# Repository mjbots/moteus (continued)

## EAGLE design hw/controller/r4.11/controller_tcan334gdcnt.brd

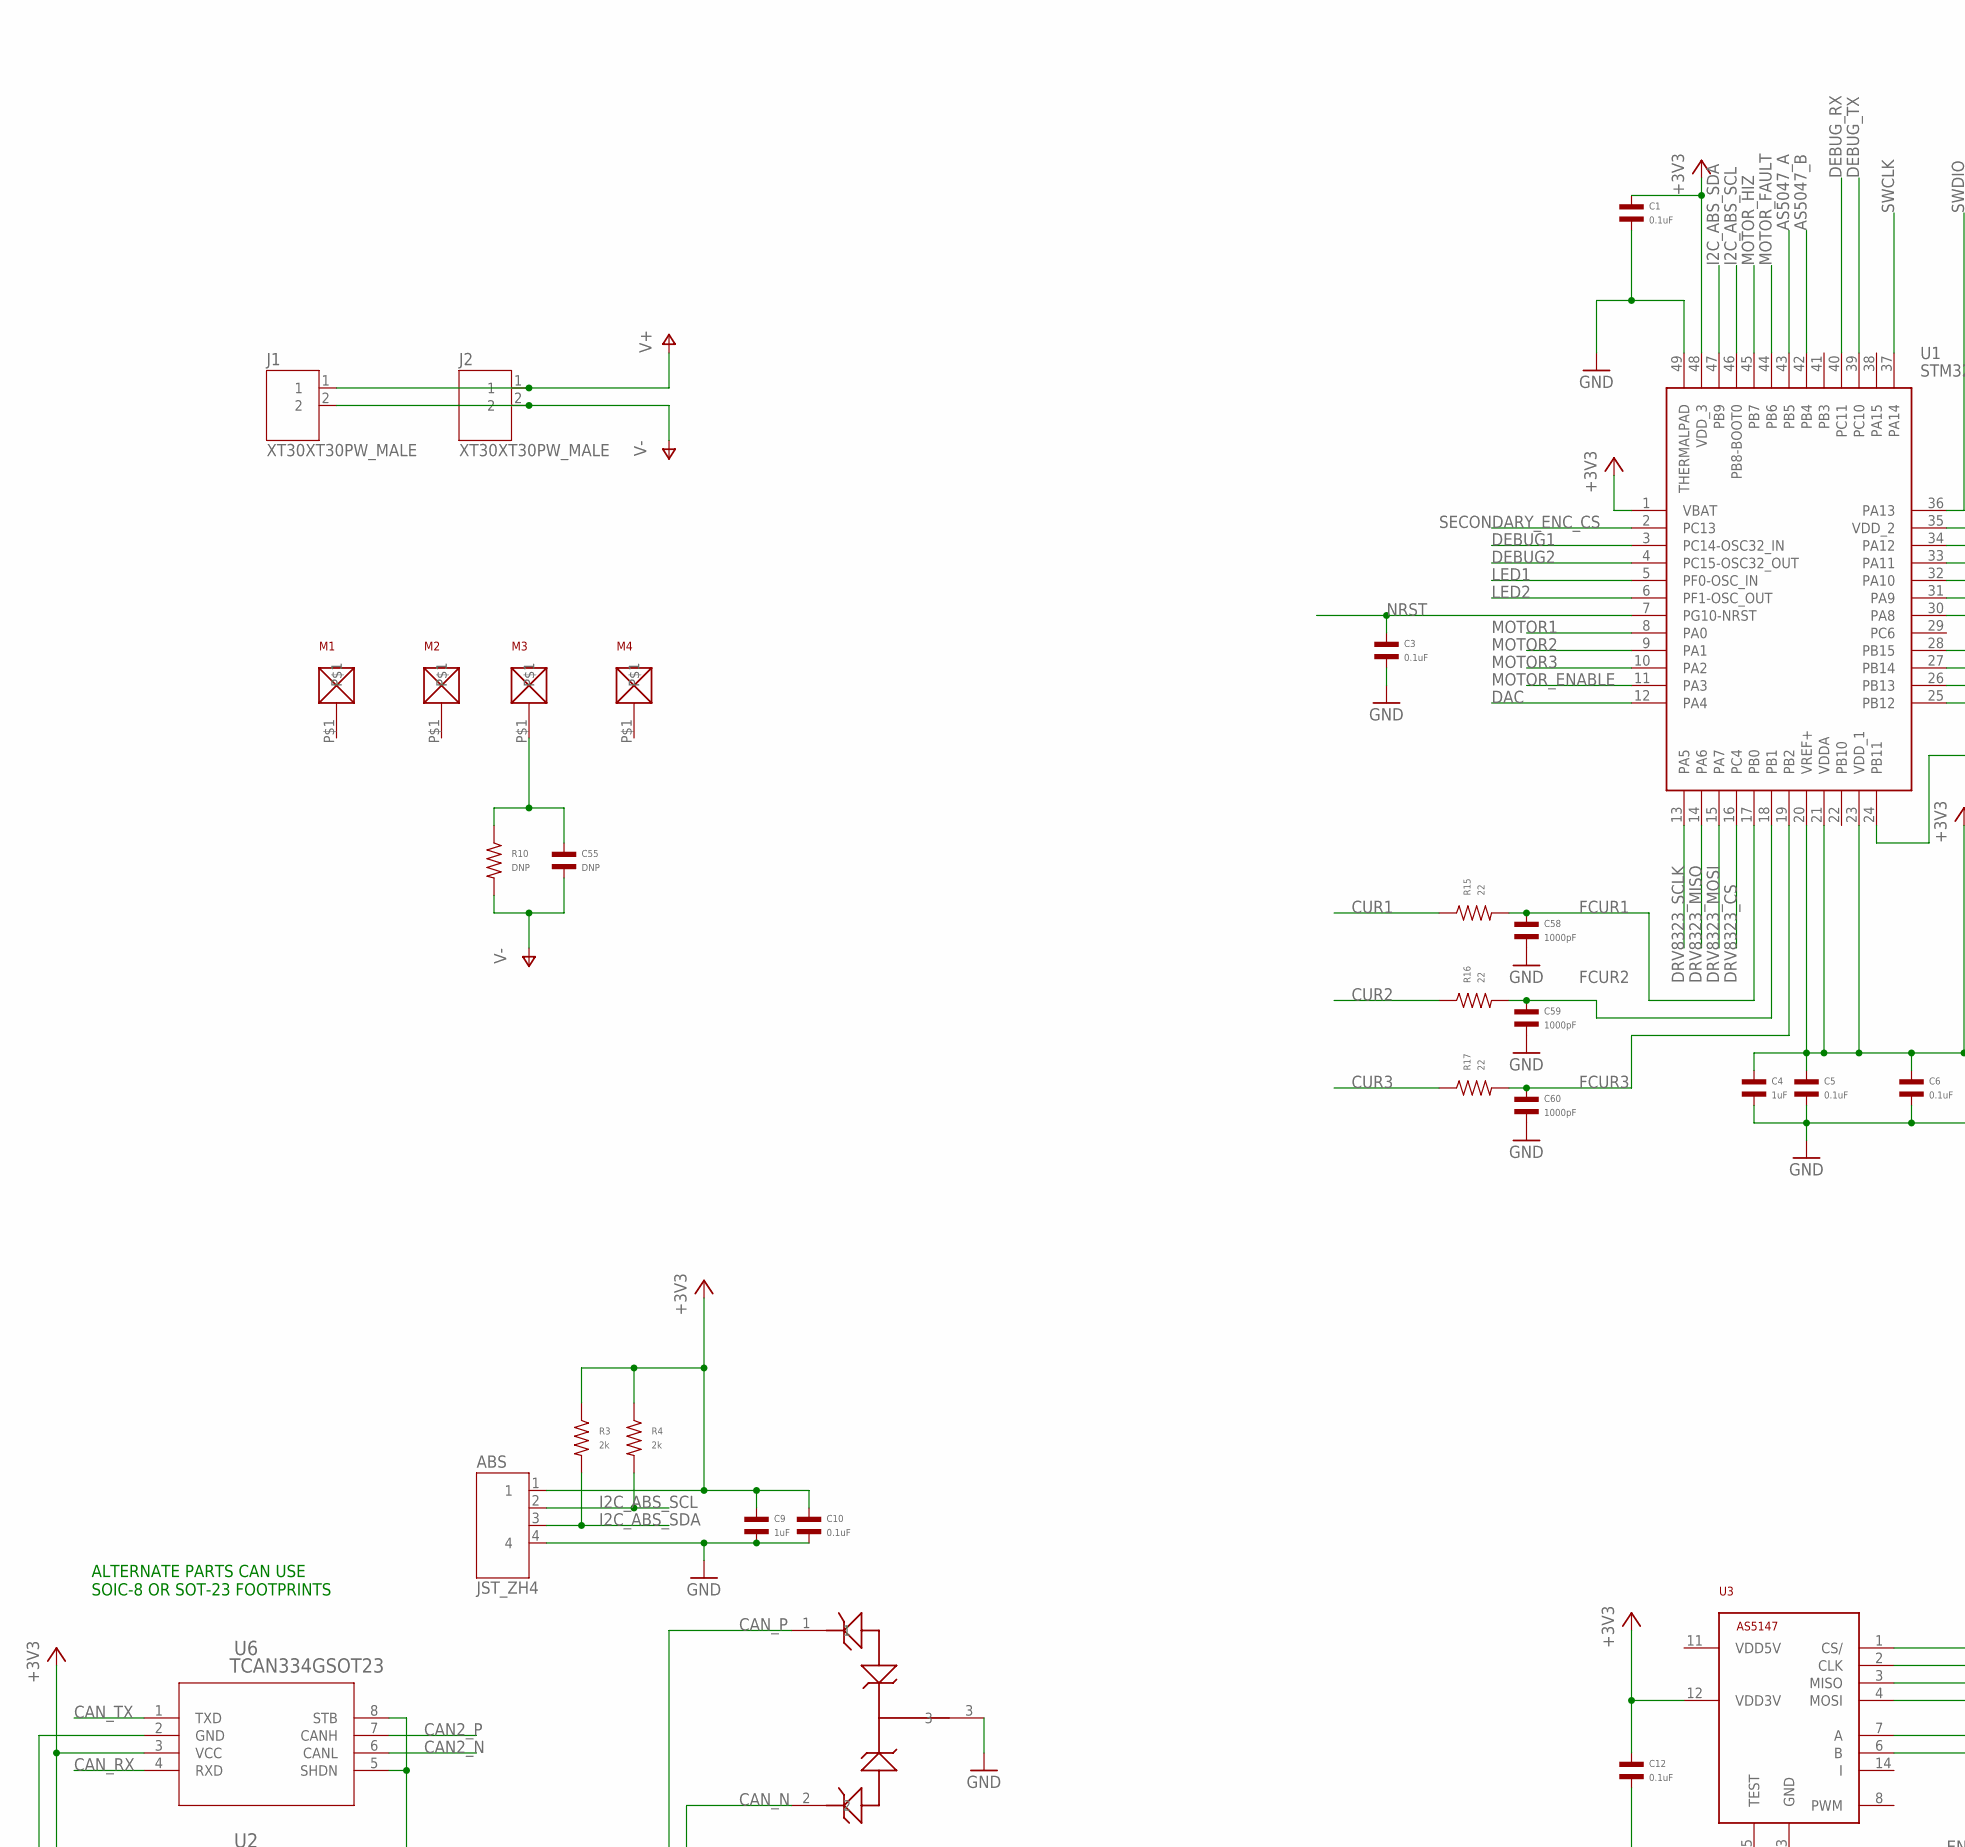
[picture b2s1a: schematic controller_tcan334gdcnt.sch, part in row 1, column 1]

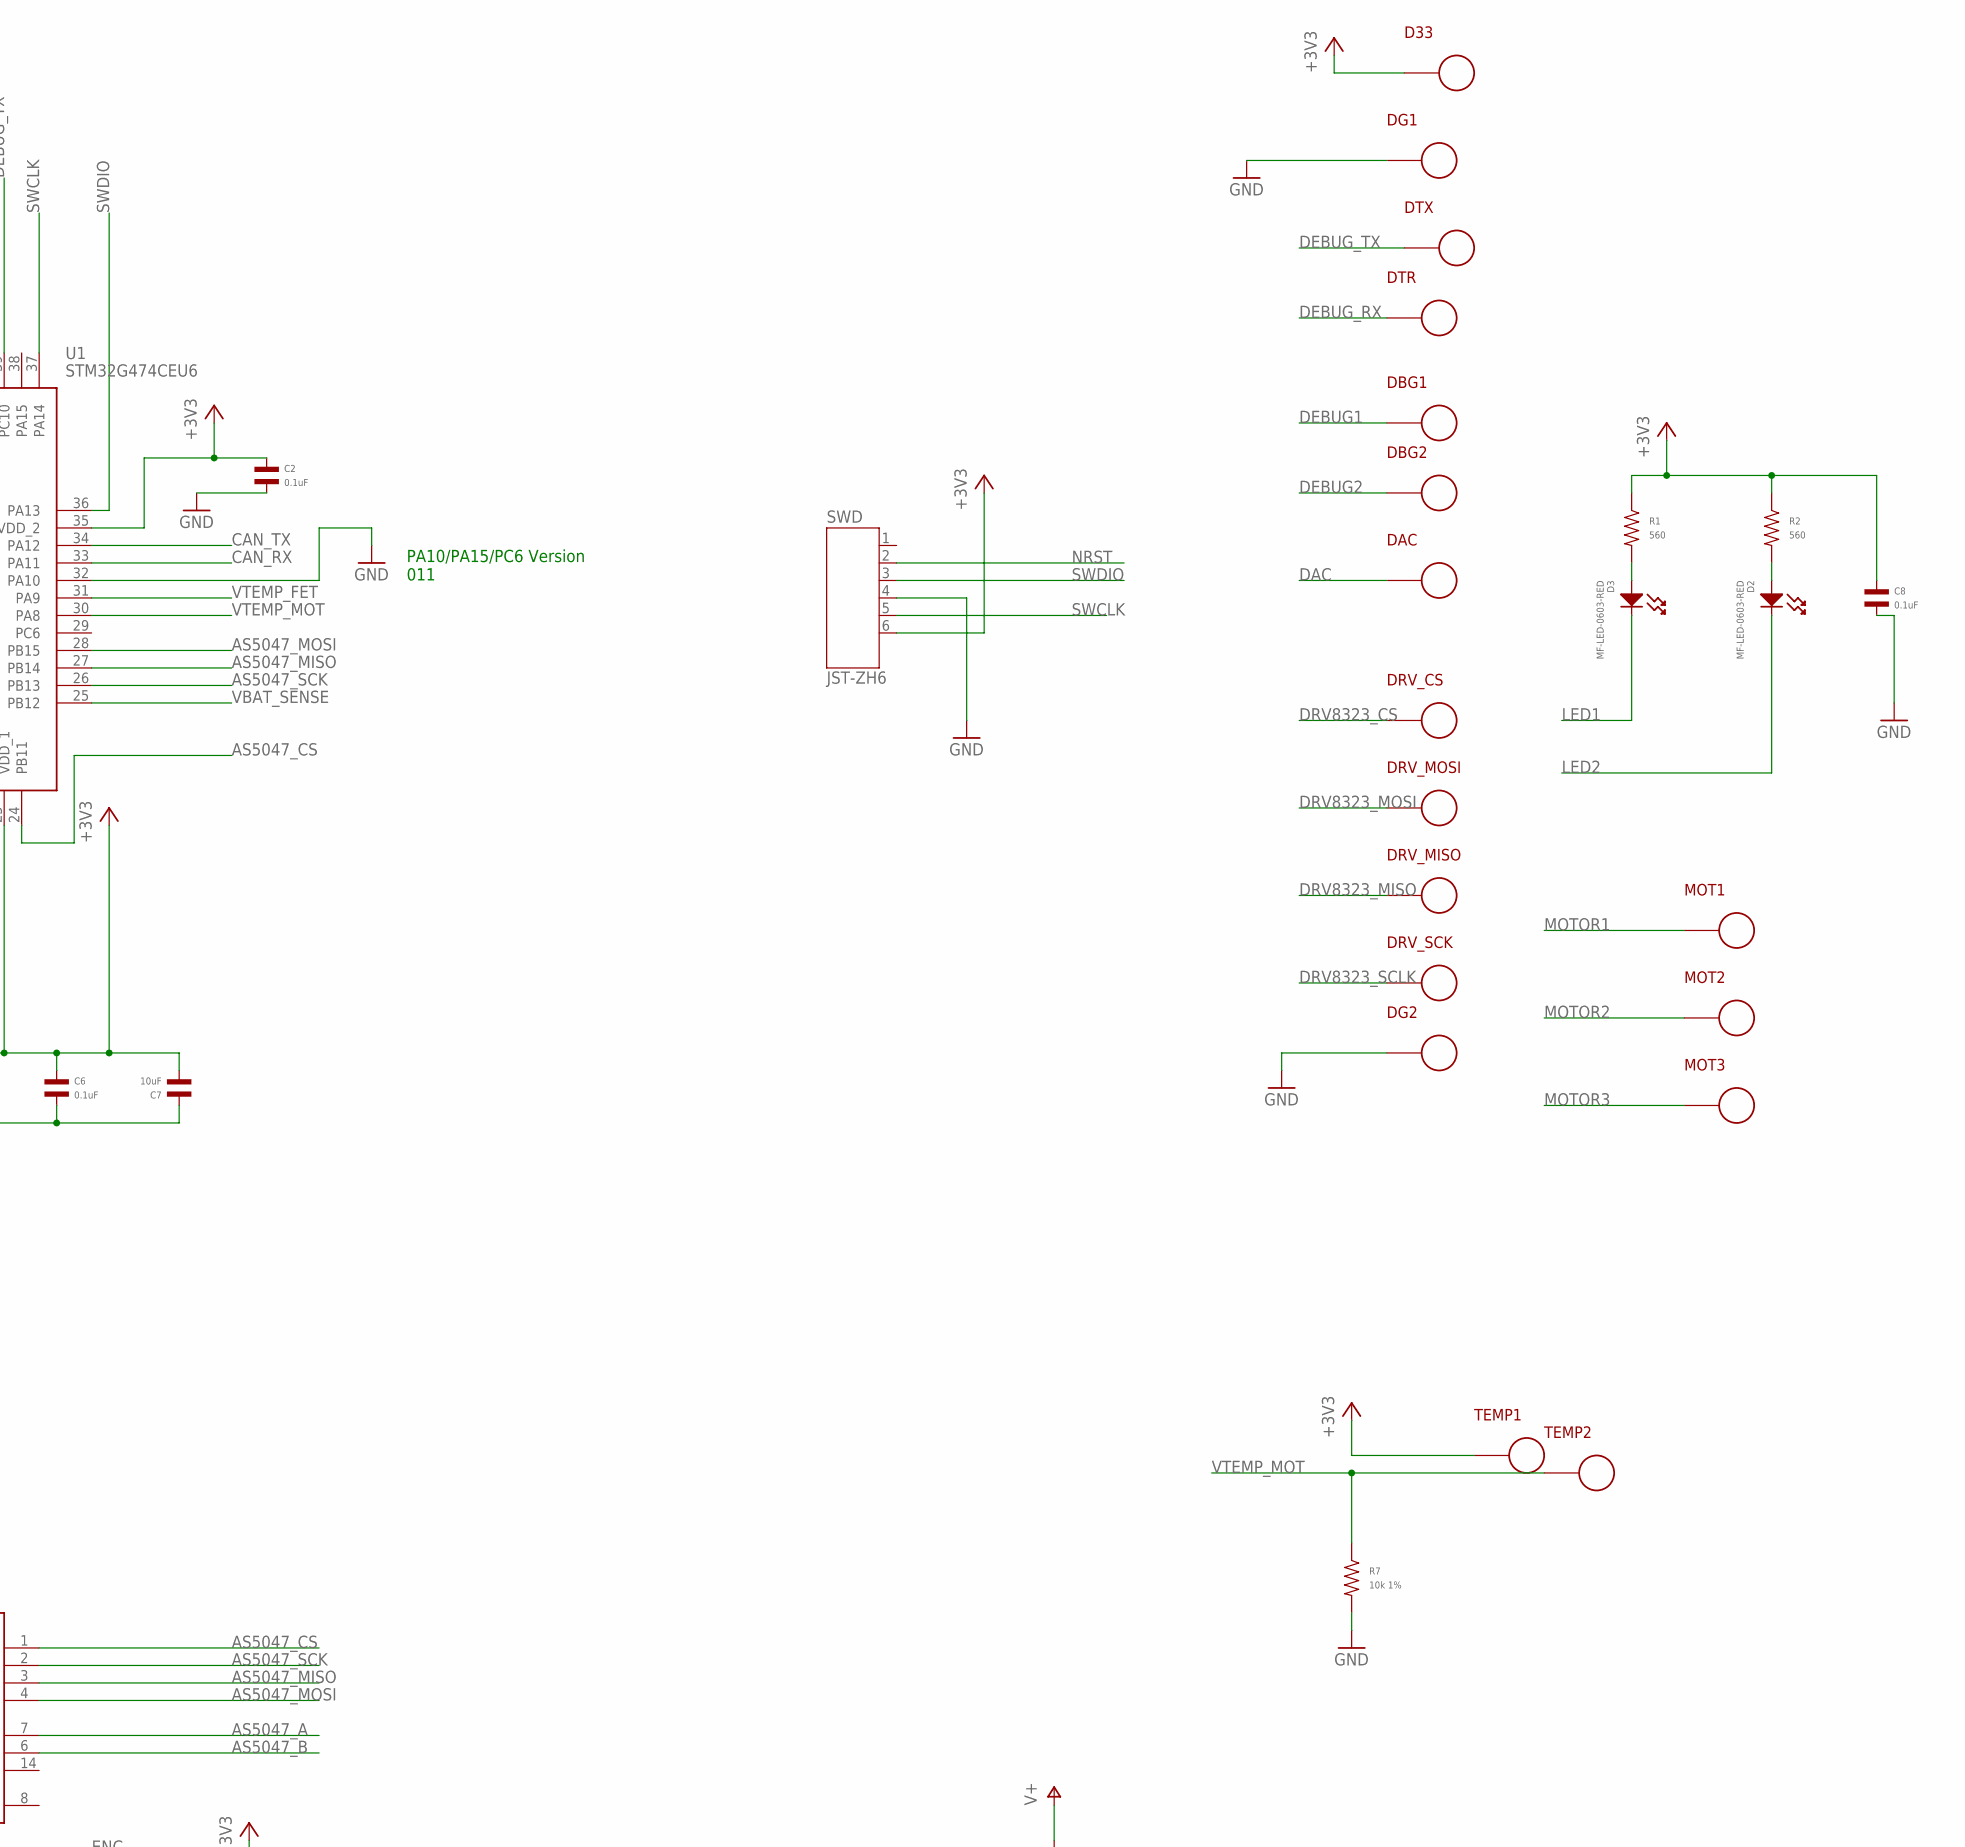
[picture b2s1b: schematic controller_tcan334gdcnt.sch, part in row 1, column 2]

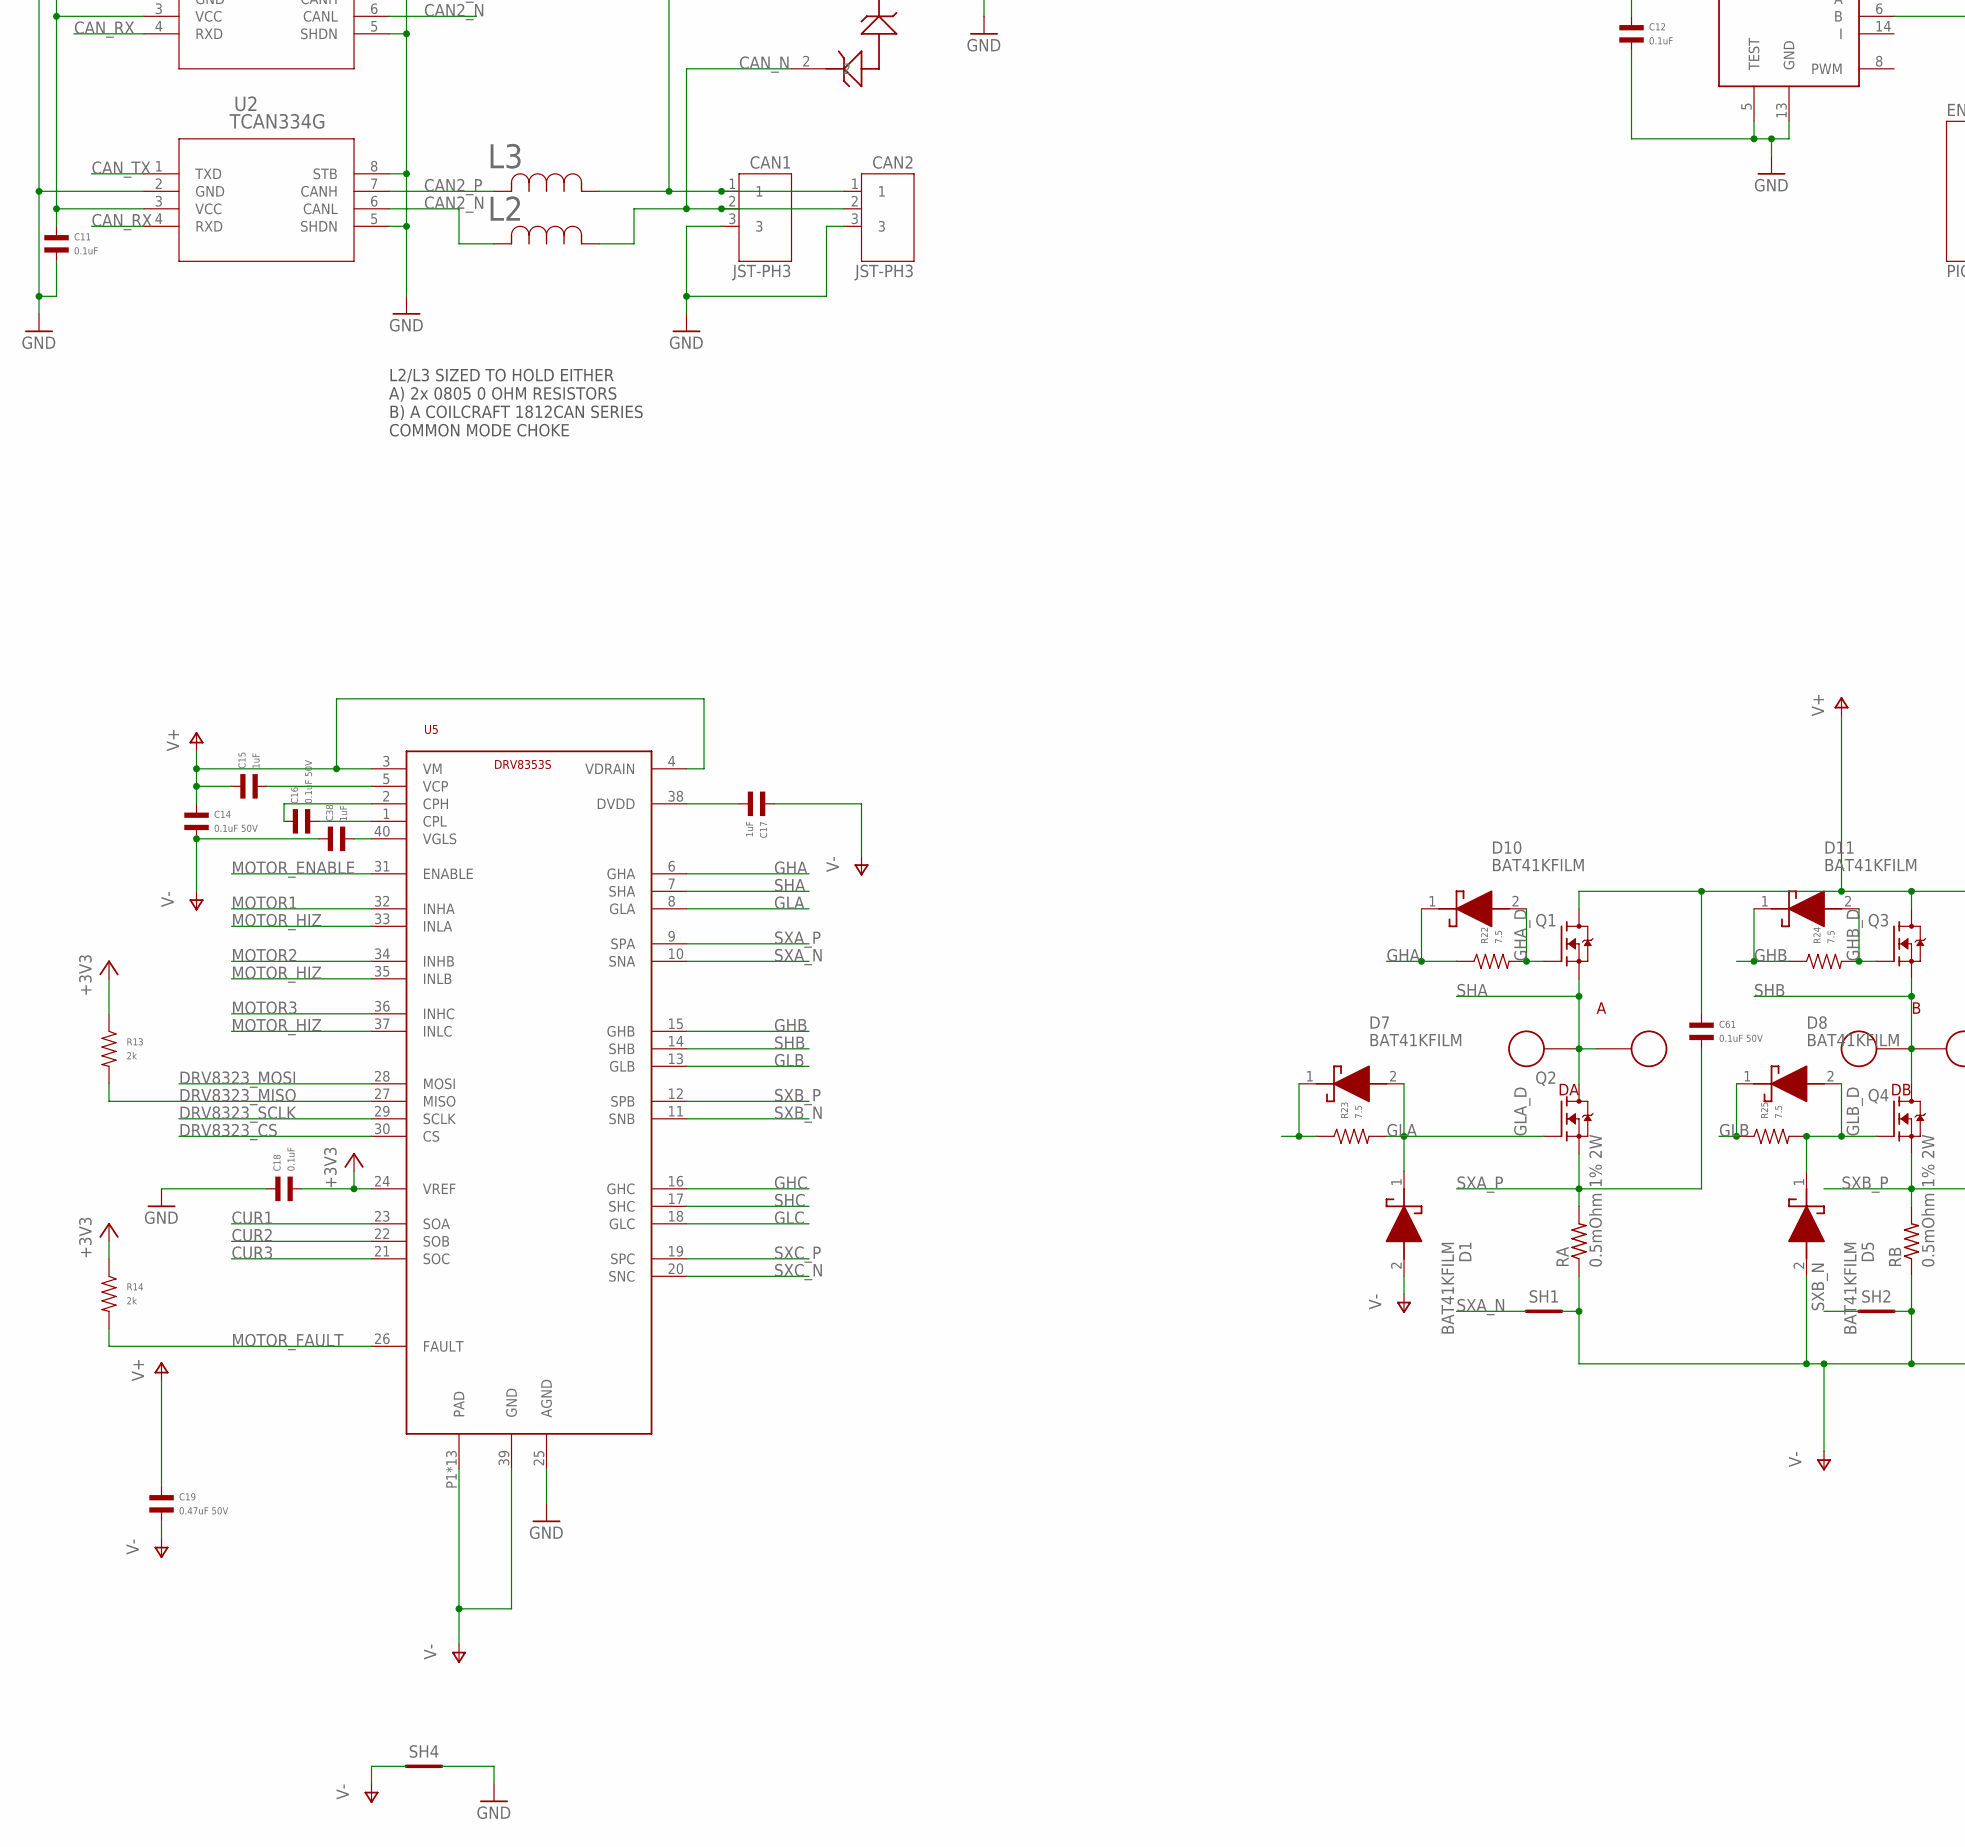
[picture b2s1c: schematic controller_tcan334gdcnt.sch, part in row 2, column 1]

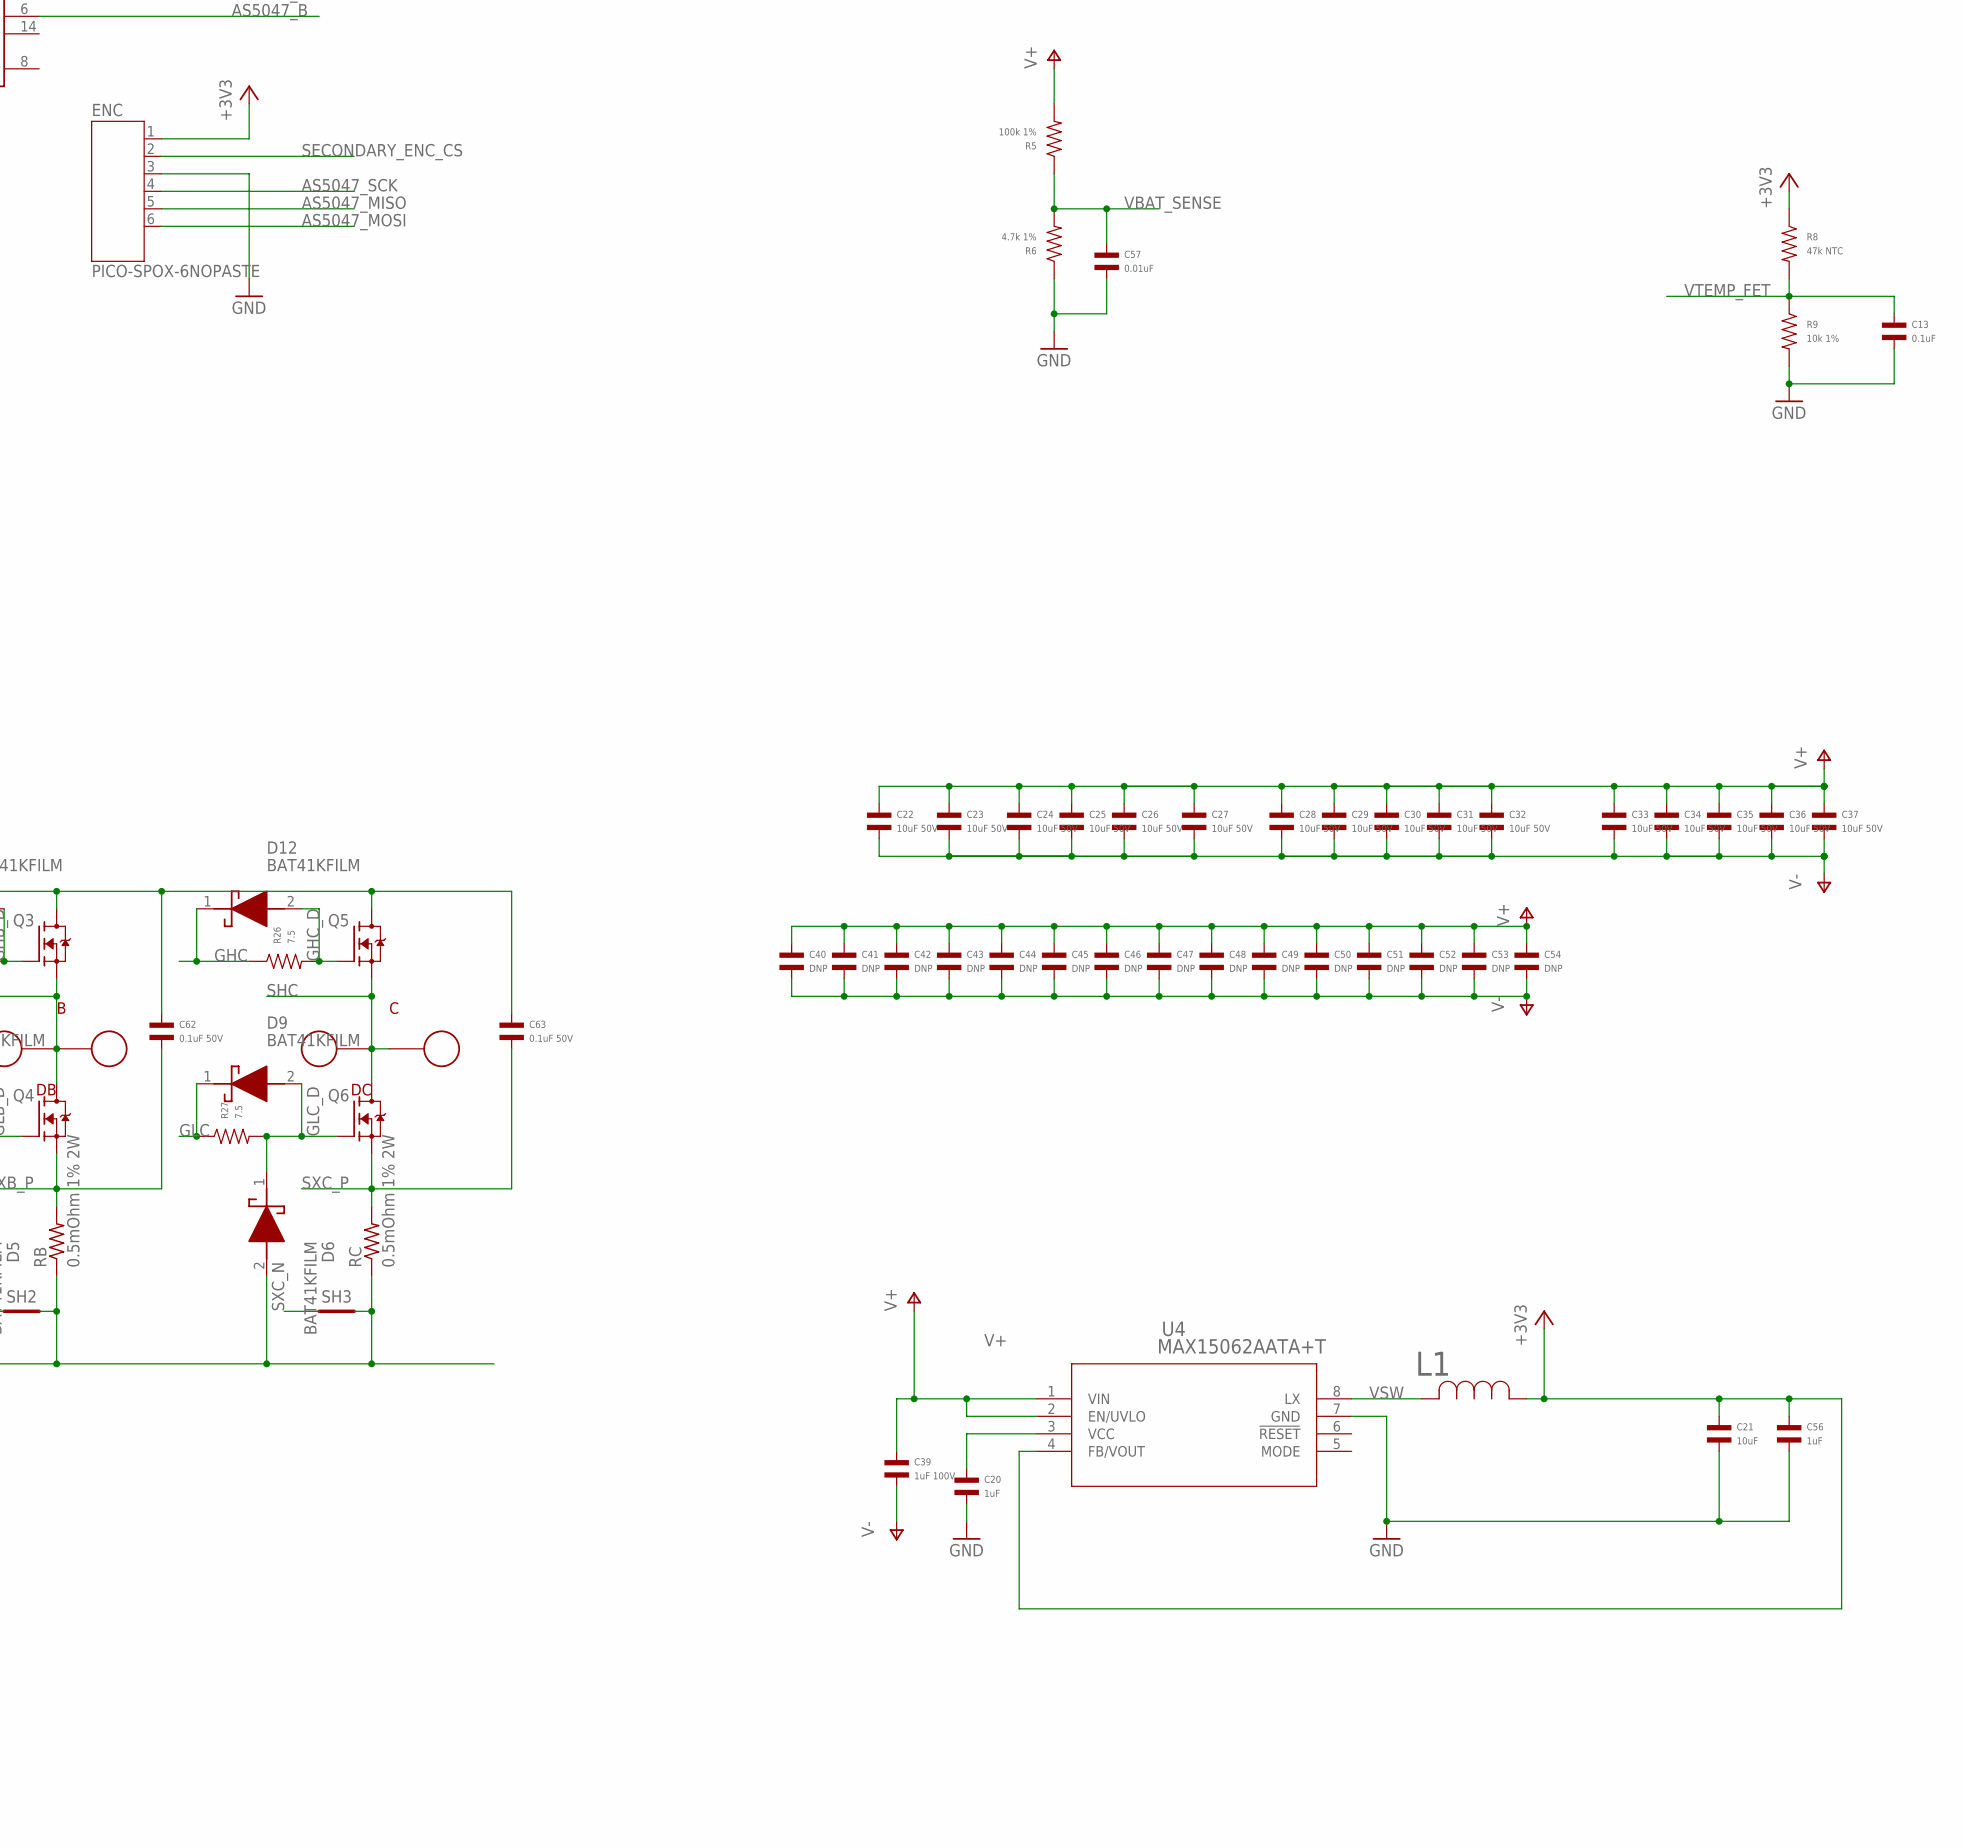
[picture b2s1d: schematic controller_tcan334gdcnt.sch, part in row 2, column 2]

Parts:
A: PAD16AWG_PAD; 16AWG_PAD
ABS: JST_ZH4; JST_S4B-ZR-SM4A-TF(LF)(SN); MPN S4B-ZR-SM4A-TF(LF)(SN)
B: PAD16AWG_PAD; 16AWG_PAD
C: PAD16AWG_PAD; 16AWG_PAD
C1, C2, C3, C5, C6, C8, C10, C12, C13, C18: 0.1uF; C0402; MPN MF-CAP-0402-0.1uF
C4, C9, C15, C17, C56: 1uF; C0402; MPN MF-CAP-0402-1uF
C7, C21: 10uF; C1206; MPN MF-CAP-1206-10uF
C11: 0.1uF; C0402_NOBORDER; MPN MF-CAP-0402-0.1uF
C14, C16: 0.1uF 50V; C0402; MPN CGA2B3X7R1H104K050BB
C19: 0.47uF 50V; C0402; MPN GRM155R61H474KE11D
C20: 1uF; C0603; MPN MF-CAP-0603-1uF
C22, C23, C24, C25, C26, C27, C28, C29, C30, C31, C32, C33, C34, C36, C37: 10uF 50V; C1206; MPN C3216X7R1H106K160AE
C35: 10uF 50V; C1206_NOBORDER; MPN C3216X7R1H106K160AE
C38: 1uF; C0603; MPN C1608X7R1E105K080AE
C39: 1uF 100V; C0805; MPN GCM21BC72A105KE36L
C40, C41, C42, C43, C44, C45, C46, C47, C48, C49, C50, C51, C52, C53, C54: DNP; C1206_NOCREAM
C55: DNP; C0402
C57: 0.01uF; C0402; MPN MF-CAP-0402-0.01uF
C58, C59, C60: 1000pF; C0402_NOBORDER; MPN MF-CAP-0402-1nF
C61, C63: 0.1uF 50V; C1206; MPN 12065C104KAZ2A
C62: 0.1uF 50V; C0603_NOBORDER; MPN 06035C104KAZ2A
CAN1, CAN2: JST-PH3; JST_S3B-PH-SM4-TB(LF)(SN); MPN S3B-PH-SM4-TB(LF)(SN)
D1, D5, D6, D7, D8, D9, D10, D11, D12: BAT41KFILM; SODFL1608X70N; MPN BAT41KFILM
D2: MF-LED-0603-RED; LED0603; MPN MF-LED-0603-GREEN
D3: MF-LED-0603-RED; LED0603
D4: DUAL_TVS; SOT23-3; MPN CDSOT23-0502B
D33: PAD24AWG_PAD; 24AWG_PAD
DA: PAD24AWG_PAD; 24AWG_PAD
DAC: PAD24AWG_PAD; 24AWG_PAD
DB: PAD24AWG_PAD; 24AWG_PAD
DBG1, DBG2: PAD24AWG_PAD; 24AWG_PAD
DC: PAD24AWG_PAD; 24AWG_PAD
DG1, DG2: PAD24AWG_PAD; 24AWG_PAD
DRV_CS: PAD24AWG_PAD; 24AWG_PAD
DRV_MISO: PAD24AWG_PAD; 24AWG_PAD
DRV_MOSI: PAD24AWG_PAD; 24AWG_PAD
DRV_SCK: PAD24AWG_PAD; 24AWG_PAD
DTR: PAD24AWG_PAD; 24AWG_PAD
DTX: PAD24AWG_PAD; 24AWG_PAD
ENC: PICO-SPOX-6NOPASTE; PICO-SPOX-SMT-RA-6-NOPASTE
J1, J2: XT30XT30PW_MALE; XT30PW_MALE
L1: SRN4018-220M; IND_BOURNS_SRN4018; MANUFACTURER_PART_NUMBER SRN4018-330M
L2, L3: HALF_CHOKE; 1812_COMMON_HALF; MPN MF-RES-0805-0
M1, M2, M3, M4: MOUNT; M2.5MOUNT
MOT1, MOT2, MOT3: PAD24AWG_PAD; 24AWG_PAD
Q1, Q2, Q3, Q4, Q5, Q6: TPH1R204PLSOP_ADVANCE_8; SOP_ADVANCE_8; MPN TPH2R506PL,L1Q
R1, R2: 560; R0402; MPN MF-RES-0402-560
R3, R4, R13, R14: 2k; R0402; MPN MF-RES-0402-2K
R5: 100k 1%; R0402; MPN RC0402FR-07100KL
R6: 4.7k 1%; R0402; MPN RC0402FR-074K7L
R7, R9: 10k 1%; R0402; MPN RC0402FR-0710KL
R8: 47k NTC; R0402; MPN NCP15WB473F03RC
R10: DNP; R0402
R15, R16, R17: 22; R0402_NOBORDER; MPN MF-RES-0402-22
R22, R23, R24, R25, R26, R27: 7.5; R0402; MPN RC0402FR-077R5L
RA: 0.5mOhm 1% 2W; M1206; MPN HCS1206FTL500
RB: 0.5mOhm 1% 2W; M1206; MPN HCS1206FTL500
RC: 0.5mOhm 1% 2W; M1206; MPN HCS1206FTL500
SH1, SH2, SH3: SHORTT5; SHORT_TOP-50
SH4: SHORTMEDIUM; SHORT_TOP-MEDIUM
SWD: JST-ZH6; JST_S6B-ZR-SM4A-TF(LF)(SN); MPN S6B-ZR-SM4A-TF(LF)(SN)
TEMP1, TEMP2: PAD24AWG_PAD; 24AWG_PAD
U1: STM32G474CEU6; QFN50P700X700X60-49N; MPN STM32G474CEU6
U2: TCAN334G; SOIC8; MPN TCAN337GDR
U3: AS5147; TSSOP14; MPN AS5047P-ATSM
U4: MAX15062AATA+T; 21-0487A_MXM; MPN MAX15062AATA+T
U5: DRV8353S; WQFN-40; MPN DRV8353FSRTAR
U6: TCAN334GSOT23; SOT23-8; MPN TCAN334GDCNT

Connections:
+3V3: ABS.1, C1.P$1, C2.P$1, C4.P$1, C5.P$1, C6.P$1, C7.P$2, C8.P$1, C9.P$1, C10.P$1, C11.P$1, C12.P$1, C18.P$2, C21.P$1, C56.P$1, D33.P$1, ENC.1, L1.1, R1.P$1, R2.P$1, R3.P$1, R4.P$1, R8.P$1, R13.P$1, R14.P$1, SWD.6, TEMP1.P$1, U1.1 (VBAT), U1.20 (VREF+), U1.21 (VDDA), U1.23 (VDD_1), U1.35 (VDD_2), U1.48 (VDD_3), U2.3 (VCC), U3.12 (VDD3V), U4.4 (FB/VOUT), U5.24 (VREF), U6.3 (VCC)
AS5047_A: U1.43 (PB5), U3.7 (A)
AS5047_B: U1.42 (PB4), U3.6 (B)
AS5047_CS: U1.24 (PB11), U3.1 (CS/)
AS5047_MISO: ENC.5, U1.27 (PB14), U3.3 (MISO)
AS5047_MOSI: ENC.6, U1.28 (PB15), U3.4 (MOSI)
AS5047_SCK: ENC.4, U1.26 (PB13), U3.2 (CLK)
CAN2_N: L2.P$2 (2), U2.6 (CANL), U6.6 (CANL)
CAN2_P: L3.P$2 (2), U2.7 (CANH), U6.7 (CANH)
CAN_N: CAN1.2, CAN2.2, D4.2, L2.P$1 (1)
CAN_P: CAN1.1, CAN2.1, D4.1, L3.P$1 (1)
CAN_RX: U1.33 (PA11), U2.4 (RXD), U6.4 (RXD)
CAN_TX: U1.34 (PA12), U2.1 (TXD), U6.1 (TXD)
CUR1: R15.P$1, U5.23 (SOA)
CUR2: R16.P$1, U5.22 (SOB)
CUR3: R17.P$1, U5.21 (SOC)
DAC: DAC.P$1, U1.12 (PA4)
DEBUG1: DBG1.P$1, U1.3 (PC14-OSC32_IN)
DEBUG2: DBG2.P$1, U1.4 (PC15-OSC32_OUT)
DEBUG_RX: DTR.P$1, U1.40 (PC11)
DEBUG_TX: DTX.P$1, U1.39 (PC10)
DRV8323_CS: DRV_CS.P$1, U1.16 (PC4), U5.30 (CS)
DRV8323_MISO: DRV_MISO.P$1, R13.P$2, U1.14 (PA6), U5.27 (MISO)
DRV8323_MOSI: DRV_MOSI.P$1, U1.15 (PA7), U5.28 (MOSI)
DRV8323_SCLK: DRV_SCK.P$1, U1.13 (PA5), U5.29 (SCLK)
FCUR1: C58.P$1, R15.P$2, U1.17 (PB0)
FCUR2: C59.P$1, R16.P$2, U1.18 (PB1)
FCUR3: C60.P$1, R17.P$2, U1.19 (PB2)
GHA: D10.1 (K), R22.P$1, U5.6 (GHA)
GHA_D: D10.2 (A), Q1.4 (G), R22.P$2
GHB: D11.1 (K), R24.P$1, U5.15 (GHB)
GHB_D: D11.2 (A), Q3.4 (G), R24.P$2
GHC: D12.1 (K), R26.P$1, U5.16 (GHC)
GHC_D: D12.2 (A), Q5.4 (G), R26.P$2
GLA: D7.1 (K), R23.P$1, U5.8 (GLA)
GLA_D: D1.1 (K), D7.2 (A), Q2.4 (G), R23.P$2
GLB: D8.1 (K), R25.P$1, U5.13 (GLB)
GLB_D: D5.1 (K), D8.2 (A), Q4.4 (G), R25.P$2
GLC: D9.1 (K), R27.P$1, U5.18 (GLC)
GLC_D: D6.1 (K), D9.2 (A), Q6.4 (G), R27.P$2
GND: ABS.4, C1.P$2, C2.P$2, C3.P$2, C4.P$2, C5.P$2, C6.P$2, C7.P$1, C8.P$2, C9.P$2, C10.P$2, C11.P$2, C12.P$2, C13.P$2, C18.P$1, C20.P$2, C21.P$2, C56.P$2, C57.P$2, C58.P$2, C59.P$2, C60.P$2, CAN1.3, CAN2.3, D4.3, DG1.P$1, DG2.P$1, ENC.3, R6.P$1, R7.P$2, R9.P$2, SH4.2, SWD.4, U1.32 (PA10), U1.49 (THERMALPAD), U2.2 (GND), U2.5 (SHDN), U2.8 (STB), U3.5 (TEST), U3.13 (GND), U4.7 (GND), U5.25 (AGND), U6.2 (GND), U6.5 (SHDN), U6.8 (STB)
I2C_ABS_SCL: ABS.2, R4.P$2, U1.46 (PB8-BOOT0)
I2C_ABS_SDA: ABS.3, R3.P$2, U1.47 (PB9)
LED1: D3.CATHODE, U1.5 (PF0-OSC_IN)
LED2: D2.CATHODE, U1.6 (PF1-OSC_OUT)
MOTOR1: MOT1.P$1, U1.8 (PA0), U5.32 (INHA)
MOTOR2: MOT2.P$1, U1.9 (PA1), U5.34 (INHB)
MOTOR3: MOT3.P$1, U1.10 (PA2), U5.36 (INHC)
MOTOR_ENABLE: U1.11 (PA3), U5.31 (ENABLE)
MOTOR_FAULT: R14.P$2, U1.44 (PB6), U5.26 (FAULT)
MOTOR_HIZ: U1.45 (PB7), U5.33 (INLA), U5.35 (INLB), U5.37 (INLC)
unnamed: C55.P$1, M3.P$1, R10.P$1
unnamed: C38.P$2, U5.40 (VGLS)
unnamed: C20.P$1, U4.3 (VCC)
unnamed: C16.P$2, U5.1 (CPL)
unnamed: C16.P$1, U5.2 (CPH)
unnamed: C15.P$2, U5.5 (VCP)
unnamed: C17.P$2, U5.38 (DVDD)
unnamed: D3.ANODE, R1.P$2
unnamed: D2.ANODE, R2.P$2
NRST: C3.P$1, SWD.2, U1.7 (PG10-NRST)
SECONDARY_ENC_CS: ENC.2, U1.2 (PC13)
SHA: A.1, DA.P$1, Q1.1 (S), Q1.2 (S), Q1.3 (S), Q2.5 (D), Q2.6 (D), Q2.7 (D), Q2.8 (D), Q2.PAD (D), U5.7 (SHA)
SHB: B.1, DB.P$1, Q3.1 (S), Q3.2 (S), Q3.3 (S), Q4.5 (D), Q4.6 (D), Q4.7 (D), Q4.8 (D), Q4.PAD (D), U5.14 (SHB)
SHC: C.1, DC.P$1, Q5.1 (S), Q5.2 (S), Q5.3 (S), Q6.5 (D), Q6.6 (D), Q6.7 (D), Q6.8 (D), Q6.PAD (D), U5.17 (SHC)
SWCLK: SWD.5, U1.37 (PA14)
SWDIO: SWD.3, U1.36 (PA13)
SXA_N: SH1.1, U5.10 (SNA)
SXA_P: C61.P$2, Q2.1 (S), Q2.2 (S), Q2.3 (S), RA.2, U5.9 (SPA)
SXB_N: SH2.1, U5.11 (SNB)
SXB_P: C62.P$2, Q4.1 (S), Q4.2 (S), Q4.3 (S), RB.2, U5.12 (SPB)
SXC_N: SH3.1, U5.20 (SNC)
SXC_P: C63.P$2, Q6.1 (S), Q6.2 (S), Q6.3 (S), RC.2, U5.19 (SPC)
V+: C14.P$1, C15.P$1, C19.P$1, C22.P$1, C23.P$1, C24.P$1, C25.P$1, C26.P$1, C27.P$1, C28.P$1, C29.P$1, C30.P$1, C31.P$1, C32.P$1, C33.P$1, C34.P$1, C35.P$1, C36.P$1, C37.P$1, C39.P$1, C40.P$1, C41.P$1, C42.P$1, C43.P$1, C44.P$1, C45.P$1, C46.P$1, C47.P$1, C48.P$1, C49.P$1, C50.P$1, C51.P$1, C52.P$1, C53.P$1, C54.P$1, C61.P$1, C62.P$1, C63.P$1, J1.1, J2.1, Q1.5 (D), Q1.6 (D), Q1.7 (D), Q1.8 (D), Q1.PAD (D), Q3.5 (D), Q3.6 (D), Q3.7 (D), Q3.8 (D), Q3.PAD (D), Q5.5 (D), Q5.6 (D), Q5.7 (D), Q5.8 (D), Q5.PAD (D), R5.P$2, U4.1 (VIN), U4.2 (EN/UVLO), U5.3 (VM), U5.4 (VDRAIN)
V-: C14.P$2, C17.P$1, C19.P$2, C22.P$2, C23.P$2, C24.P$2, C25.P$2, C26.P$2, C27.P$2, C28.P$2, C29.P$2, C30.P$2, C31.P$2, C32.P$2, C33.P$2, C34.P$2, C35.P$2, C36.P$2, C37.P$2, C38.P$1, C39.P$2, C40.P$2, C41.P$2, C42.P$2, C43.P$2, C44.P$2, C45.P$2, C46.P$2, C47.P$2, C48.P$2, C49.P$2, C50.P$2, C51.P$2, C52.P$2, C53.P$2, C54.P$2, C55.P$2, D1.2 (A), D5.2 (A), D6.2 (A), J1.2, J2.2, R10.P$2, RA.1, RB.1, RC.1, SH1.2, SH2.2, SH3.2, SH4.1, U5.39 (GND), U5.P1 (PAD), U5.P2 (PAD), U5.P3 (PAD), U5.P7 (PAD), U5.P8 (PAD), U5.P9 (PAD), U5.P12 (PAD), U5.P13 (PAD), U5.P14 (PAD), U5.P17 (PAD), U5.P18 (PAD), U5.P19 (PAD), U5.PAD
VBAT_SENSE: C57.P$1, R5.P$1, R6.P$2, U1.25 (PB12)
VSW: L1.2, U4.8 (LX)
VTEMP_FET: C13.P$1, R8.P$2, R9.P$1, U1.31 (PA9)
VTEMP_MOT: R7.P$1, TEMP2.P$1, U1.30 (PA8)

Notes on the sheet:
PA10/PA15/PC6 Version 011
L2/L3 SIZED TO HOLD EITHER A) 2x 0805 0 OHM RESISTORS B) A COILCRAFT 1812CAN SERIES COMMON MODE CHOKE
ALTERNATE PARTS CAN USE SOIC-8 OR SOT-23 FOOTPRINTS

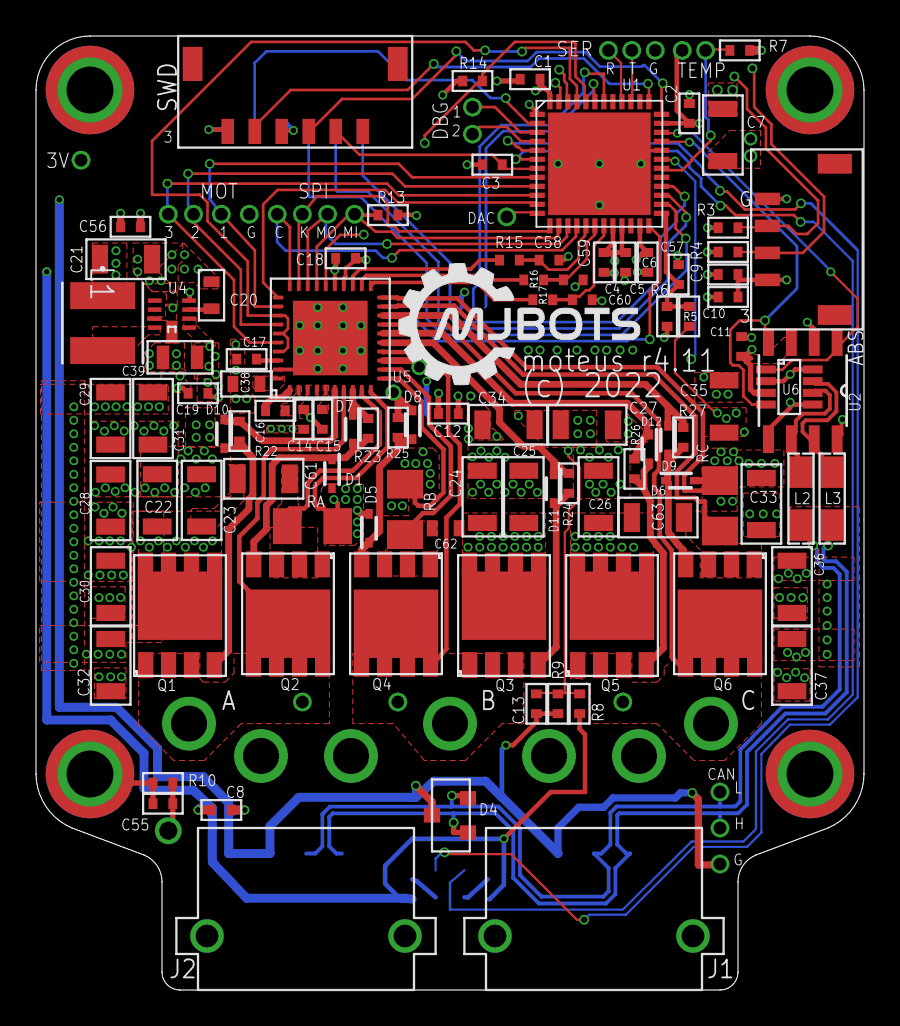
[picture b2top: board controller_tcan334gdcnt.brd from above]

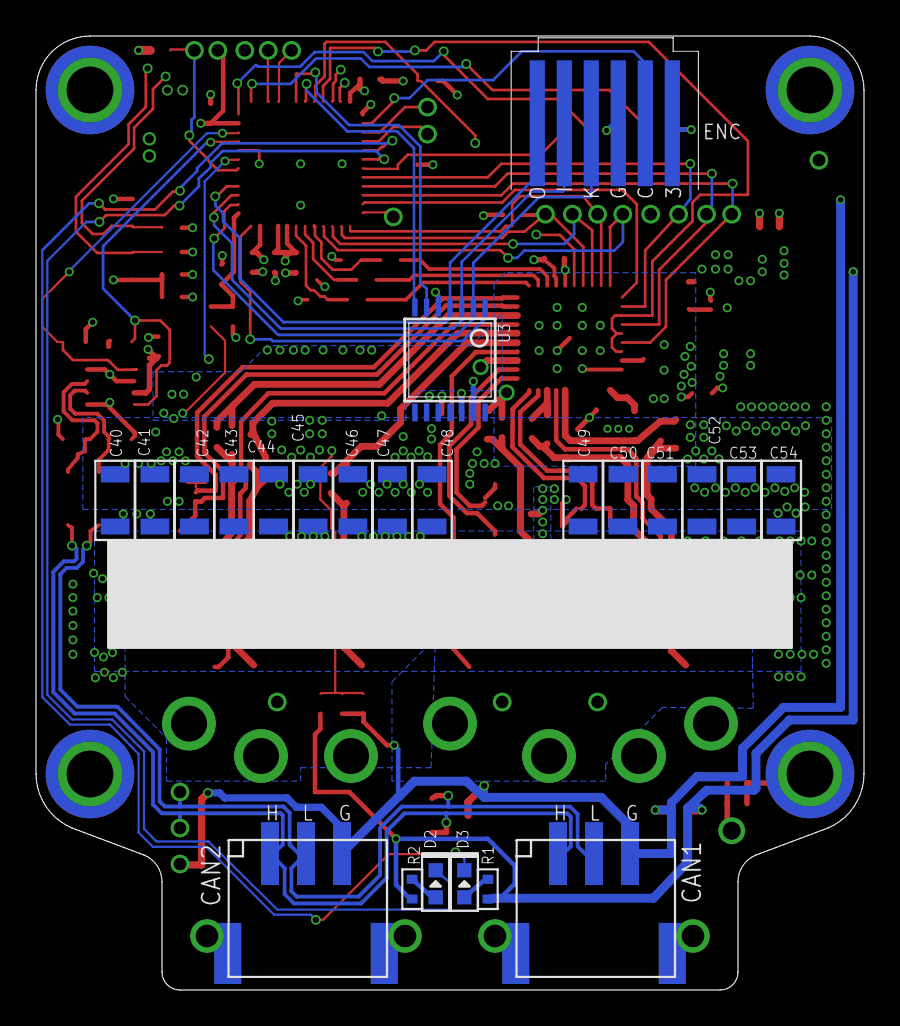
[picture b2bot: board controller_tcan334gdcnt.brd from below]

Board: 4 copper layers, 46.0 x 53.0 mm, 152 parts (23 on the bottom side), 79 nets.

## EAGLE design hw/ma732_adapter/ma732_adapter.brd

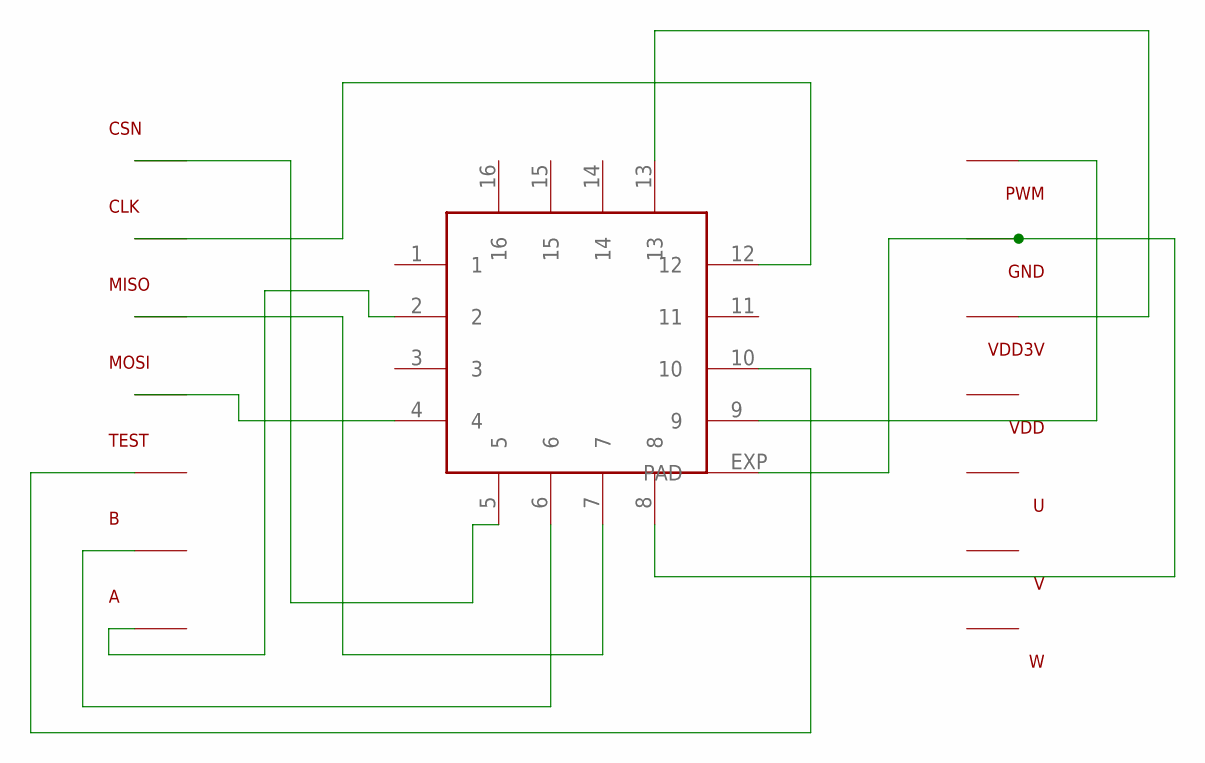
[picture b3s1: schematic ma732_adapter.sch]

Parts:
A: TSSOP_PAD
B: TSSOP_PAD
CLK: TSSOP_PAD
CSN: TSSOP_PAD
GND: TSSOP_PAD
MISO: TSSOP_PAD
MOSI: TSSOP_PAD
PWM: TSSOP_PAD
TEST: TSSOP_PAD
U: TSSOP_PAD
U$1: QFN16-BO; QFN16
V: TSSOP_PAD
VDD, VDD3V: TSSOP_PAD
W: TSSOP_PAD

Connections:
unnamed: CSN.P$1, U$1.5
unnamed: CLK.P$1, U$1.12
unnamed: MISO.P$1, U$1.7
unnamed: MOSI.P$1, U$1.4
unnamed: TEST.P$1, U$1.10
unnamed: B.P$1, U$1.6
unnamed: A.P$1, U$1.2
unnamed: PWM.P$1, U$1.9
unnamed: GND.P$1, U$1.8, U$1.EXP (PAD)
unnamed: U$1.13, VDD3V.P$1

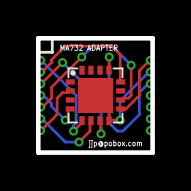
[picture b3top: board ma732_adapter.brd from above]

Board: 2 copper layers, 6.3 x 6.3 mm, 15 parts (0 on the bottom side), 10 nets.
